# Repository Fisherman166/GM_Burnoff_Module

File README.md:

# GM Burnoff Module

This repository includes a circuit which mimics the OEM burnoff module functionality. Burnoff modules are found in 1985 GM TPI cars including Corvette, Camaro, and Firebird. Feel free to modify this circuit as you see fit - I don't claim to be an analog eletronics expert.

**NOTE:  As far as I know this circuit should work as intended. Measurements from a working burnoff module in a car and the specifications from the repair manual match the design output. With that said, its never been tested in a real car, and has only been tested on a testbench. So use it at your own risk. I do not take any responsbility for any damage done.**

## Overview
* Building_your_pcb.odt - Tutorial style document which describes how to use this repository to build your own replacement burnoff module.
* OEM_Burnoff_Module_Specification.odt - Document which describes the OEM burnoff module functionality in detail.
* Design_Document.odt - Document which describes both the why and how design decisions were made for the replacement circuit.

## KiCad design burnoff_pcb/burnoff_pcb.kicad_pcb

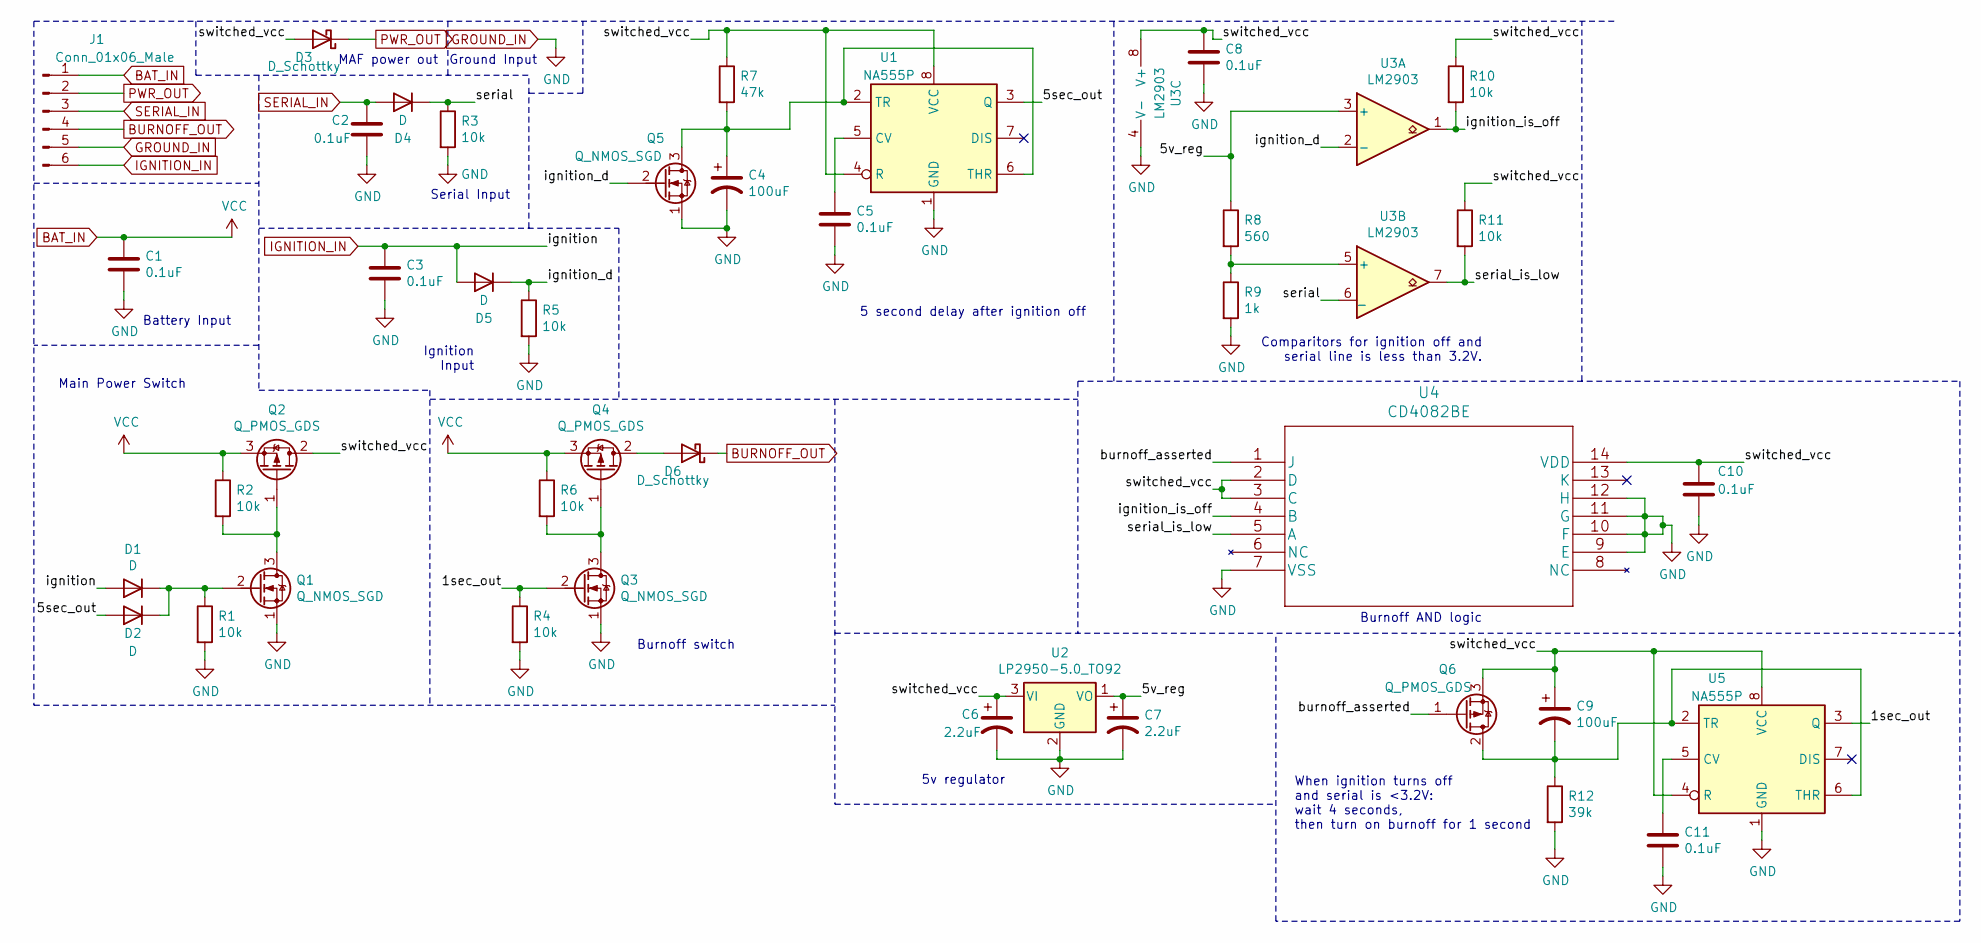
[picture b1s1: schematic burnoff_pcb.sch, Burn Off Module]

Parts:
C1, C2, C3, C5, C8, C10, C11: 0.1uF; C_Rect_L4.0mm_W2.5mm_P2.50mm
C4, C9: 100uF; CP_Radial_D8.0mm_P3.50mm
C6, C7: 2.2uF; CP_Radial_D5.0mm_P2.00mm
D1, D2, D4, D5: D; D_DO-41_SOD81_P7.62mm_Horizontal
D3, D6: D_Schottky; D_DO-201AD_P12.70mm_Horizontal
J1: Conn_01x06_Male; SolderWire-1.5sqmm_1x06_P7.8mm_D1.7mm_OD3.9mm
Q1, Q3, Q5: Q_NMOS_SGD; TO-92-3_Formed_Leads
Q2, Q4, Q6: Q_PMOS_GDS; TO-251-3_Vertical
R1, R2, R3, R4, R5, R6, R10, R11: 10k; R_Axial_DIN0207_L6.3mm_D2.5mm_P7.62mm_Horizontal
R7: 47k; R_Axial_DIN0207_L6.3mm_D2.5mm_P7.62mm_Horizontal
R8: 560; R_Axial_DIN0207_L6.3mm_D2.5mm_P7.62mm_Horizontal
R9: 1k; R_Axial_DIN0207_L6.3mm_D2.5mm_P7.62mm_Horizontal
R12: 39k; R_Axial_DIN0207_L6.3mm_D2.5mm_P7.62mm_Horizontal
U1, U5: NA555P; DIP-8_W7.62mm
U2: LP2950-5.0_TO92; TO-92-3
U3: LM2903; DIP-8_W7.62mm
U4: CD4082BE

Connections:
/1sec_out: Q3.2 (G), R4.1, U5.3 (Q)
/5sec_out: D2.2 (A), U1.3 (Q)
/5v_reg: C7.1, R8.1, U2.1 (VO), U3.3 (+)
/burnoff_asserted: Q6.1 (G), U4.1 (J)
/ignition_d: D5.1 (K), Q5.2 (G), R5.1, U3.2 (-)
/ignition_is_off: R10.2, U3.1, U4.4 (B)
/serial: D4.1 (K), R3.1, U3.6 (_)
/serial_is_low: R11.2, U3.7, U4.5 (A)
/switched_vcc: C6.1, C8.1, C9.1, C10.1, D3.2 (A), Q2.2 (D), Q6.3 (S), R7.1, R10.1, R11.1, U1.4 (R), U1.8 (VCC), U2.3 (VI), U3.8 (V+), U4.2 (D), U4.3 (C), U4.14 (VDD), U5.4 (R), U5.8 (VCC)
BAT_IN: C1.1, J1.1, Q2.3 (S), Q4.3 (S), R2.1, R6.1
BURNOFF_OUT: D6.1 (K), J1.4
GROUND_IN: C1.2, C2.2, C3.2, C4.2, C5.2, C6.2, C7.2, C8.2, C10.2, C11.2, J1.5, Q1.1 (S), Q3.1 (S), Q5.1 (S), R1.2, R3.2, R4.2, R5.2, R9.2, R12.2, U1.1 (GND), U2.2 (GND), U3.4 (V-), U4.7 (VSS), U4.9 (E), U4.10 (F), U4.11 (G), U4.12 (H), U5.1 (GND)
IGNITION_IN: C3.1, D1.2 (A), D5.2 (A), J1.6
unnamed: C4.1, Q5.3 (D), R7.2, U1.2 (TR), U1.6 (THR)
unnamed: C5.1, U1.5 (CV)
unnamed: C9.2, Q6.2 (D), R12.1, U5.2 (TR), U5.6 (THR)
unnamed: C11.1, U5.5 (CV)
unnamed: D1.1 (K), D2.1 (K), Q1.2 (G), R1.1
unnamed: D6.2 (A), Q4.2 (D)
unnamed: Q1.3 (D), Q2.1 (G), R2.2
unnamed: Q3.3 (D), Q4.1 (G), R6.2
unnamed: R8.2, R9.1, U3.5 (+)
PWR_OUT: D3.1 (K), J1.2
SERIAL_IN: C2.1, D4.2 (A), J1.3

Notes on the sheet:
Main Power Switch
Battery Input
MAF power out
Serial Input
Ground Input
Ignition Input
Burnoff switch
5 second delay after ignition off
5v regulator
Comparitors for ignition off and serial line is less than 3.2V.
Burnoff AND logic
When ignition turns off and serial is <3.2V: wait 4 seconds, then turn on burnoff for 1 second

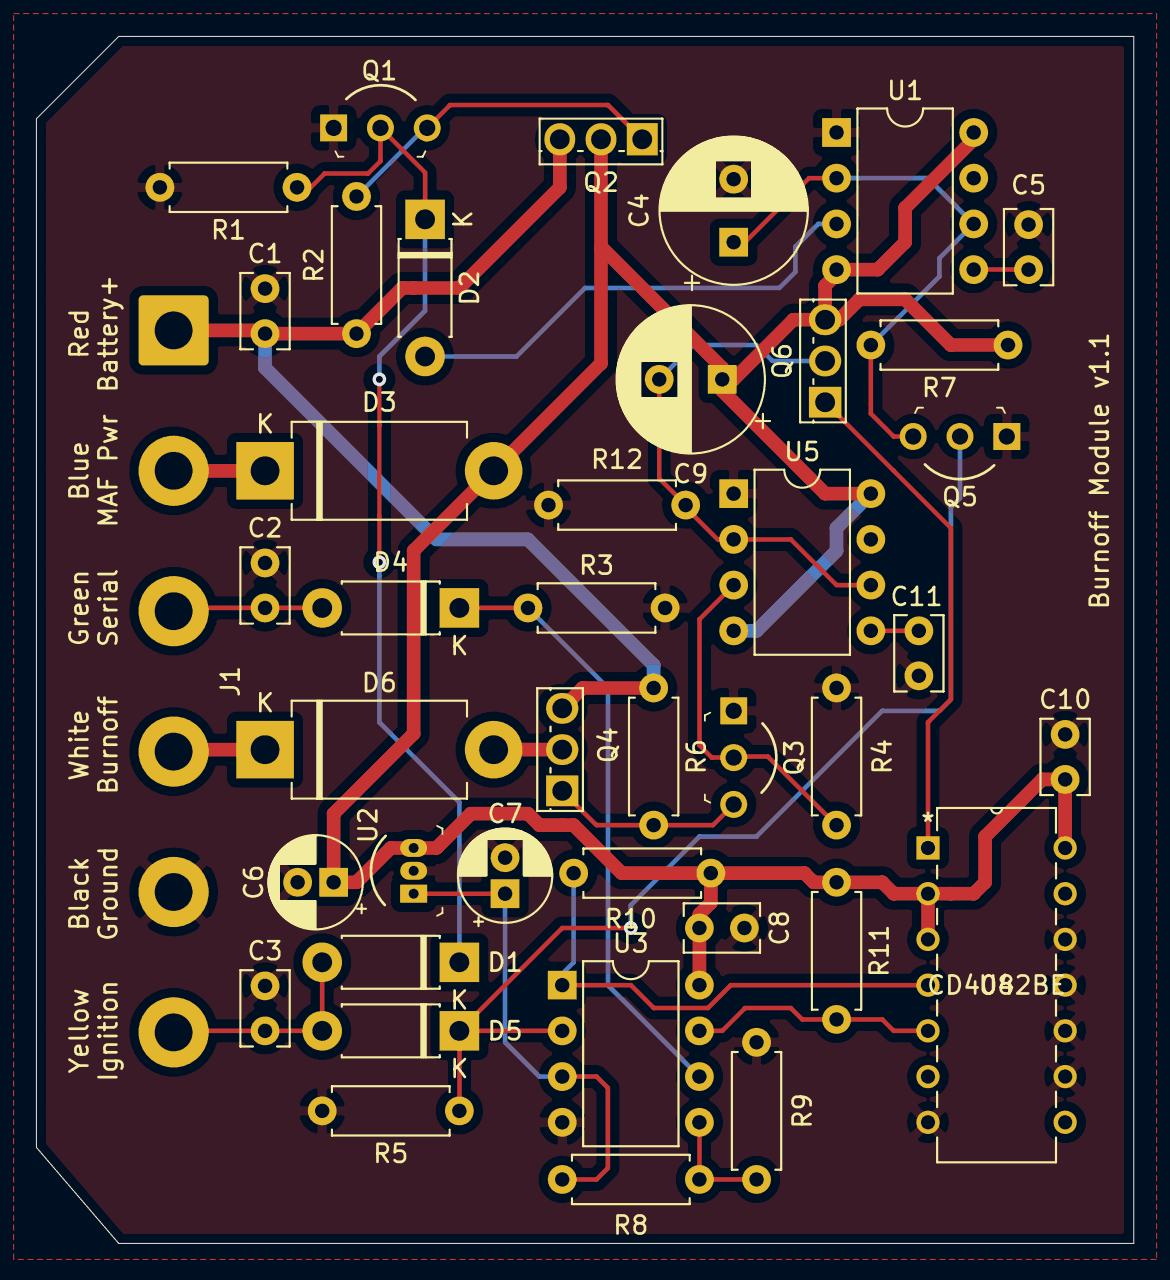
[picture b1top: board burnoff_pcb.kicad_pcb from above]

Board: 2 copper layers, 61.0 x 67.1 mm, 41 parts (0 on the bottom side), 24 nets.

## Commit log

2021-10-30 Initial commit of v1.0 of the pcb.
2021-10-30 Add first draft of OEM module spec.
2021-11-14 Revision v1.1 of the board.
2021-11-14 Remove csv version of BOM.
2021-11-14 Update documentation.
2021-11-18 Update to version v1.1 of the schematic/pcb layout.
2022-09-04 Add waveforms and results section to design document.
2022-09-05 Add pictures of PCB
2022-09-05 Add document to explain building the PCB.
2022-09-05 Add license.
2022-09-05 update readme.
2022-12-24 Updated BOM with new p-channel MOSFET as original one is EOL at the end of 2022.

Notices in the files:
burnoff_pcb/burnoff_pcb.kicad_pcb:
License: CC BY 4.0
burnoff_pcb/burnoff_pcb.sch:
creativecommons.org/licenses/by/4.0
parts and their libraries:
Copyright 2021 Accelerated Designs. All rights reserved.
